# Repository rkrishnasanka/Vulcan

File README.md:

# Vulcan

This repository will hold all information regarding future microfluidic primitives. 
Please update the software and hardware readmes as well as the engineering addendum on completing a primitive.

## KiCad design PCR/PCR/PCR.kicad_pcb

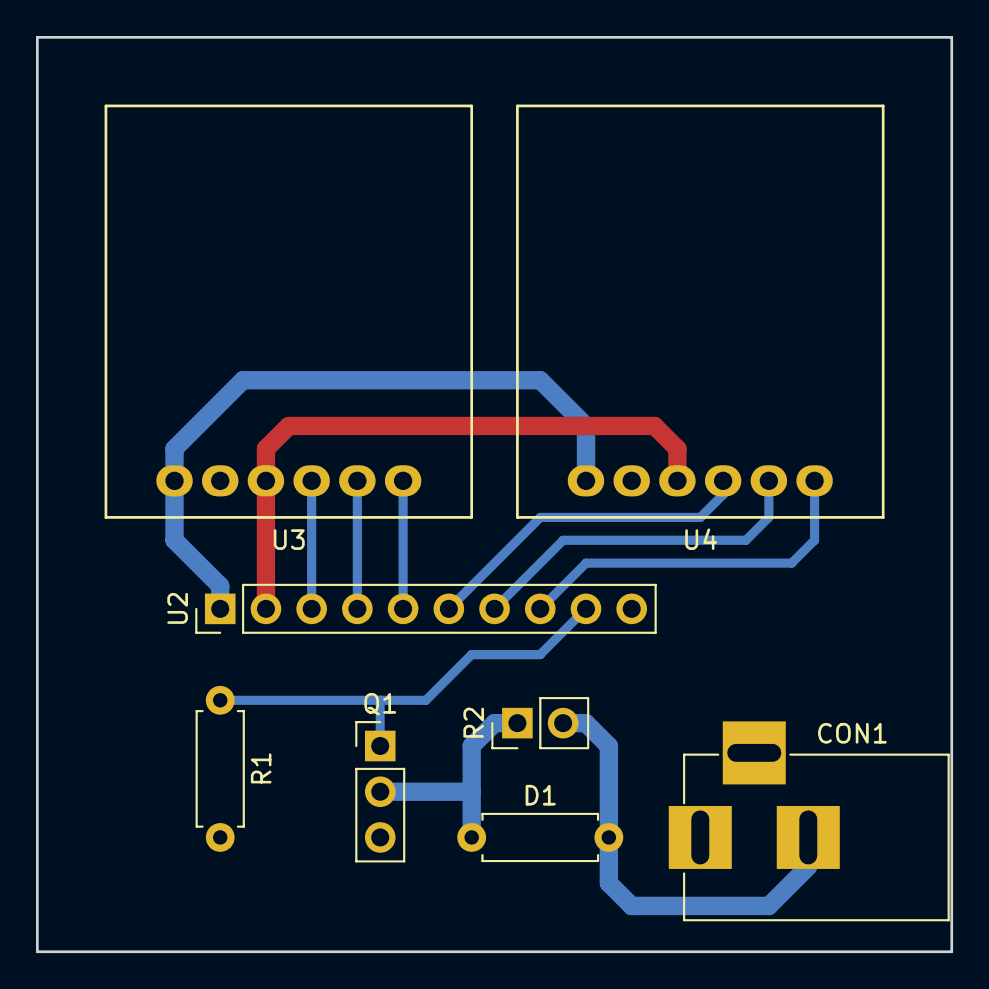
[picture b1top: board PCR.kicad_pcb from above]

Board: 2 copper layers, 50.8 x 50.8 mm, 8 parts (0 on the bottom side), 12 nets.

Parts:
CON1: BARREL_JACK
D1: D; R_Axial_DIN0207_L6.3mm_D2.5mm_P7.62mm_Horizontal
Q1: BUZ11; Pin_Header_Straight_1x03_Pitch2.54mm
R1: R; R_Axial_DIN0207_L6.3mm_D2.5mm_P7.62mm_Horizontal
R2: Nichrome Wire; Pin_Header_Straight_1x02_Pitch2.54mm
U2: Arduino; Arduino_Pin_Header_1x10
U3, U4: Amplifier; thermo_amp

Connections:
unnamed: CON1.1, Q1.3, R1.2, U2.16
unnamed: CON1.2, D1.2, R2.2
unnamed: D1.1, Q1.2, R2.1
unnamed: Q1.1, R1.1, U2.3
unnamed: U2.4, U4.6
unnamed: U2.5, U4.5
unnamed: U2.6, U4.4
unnamed: U2.10, U3.6
unnamed: U2.11, U3.5
unnamed: U2.12, U3.4
unnamed: U2.13, U3.1, U4.1
unnamed: U2.17, U3.3, U4.3

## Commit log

2016-11-13 Initial commit, pushing characterization stuff
2016-11-13 Added some text to the readme
2016-11-13 Created separate file for first deiliverables testing
2016-11-13 Updating readme, setting up git train stuff
2016-11-13 Testing out RGB values
2016-11-13 Issues with numpy array indexing
2016-11-15 Finished testing lul
2016-11-29 Updating the first deliverables code
2016-11-29 PCR beginning files in Arduino
2016-12-05 kicad
2017-01-10 Single Channel analysis
2017-01-10 Changing naming for clarity
2017-01-10 Changing naming for clarity [helloWorld/] -> [Characterization_Dev/]
2017-01-11 Created packages for format infrastructure
2017-01-17 Successfully characterizing y and x major videos, beginning to modularize and package functions
2017-01-17 Removing extraneous variables
2017-01-17 Organized computational functions into static utility class
2017-01-17 Integrated utility class function calls in programs
2017-01-25 Hello World with picam and microscope
2017-02-01 Fixed branch divergence, working on DE meeting / gather data for Ali
2017-02-02 Trying multiple techniques on video, no avail
2017-02-04 Messing around with new techniques, so close :')
2017-02-04 Drawing convex hulls, still seeing some disconnected regions, will need to look into combining close contours
2017-02-05 Got convex hulls to draw, no visible chages though.
2017-02-06 Multi thresholding and multi layer contour and convexHulls
2017-02-13 Testing configurations for multidroplet videos
2017-02-14 Significantly reduced multi counted droplets
2017-02-15 Readying the second deliverables tests
2017-02-27 State after DOug's Feb check-in, been neglecting to commit :/
2017-02-27 Refactoring for readability and comprehension
2017-02-27 Added counts between droplets (space between each) and counts during eclipses (how long a droplet takes to cross the zone)
2017-02-27 Adding a null video condition to default to connected camera (video0)
2017-02-28 Successful serial loopback test
2017-02-28 Successfully tested serial loop back with read / write loops
2017-02-28 Reformatted to use subprocess instead of os, which is its strict superset
2017-02-28 Appending to frame data to list
2017-03-02 Successful communication between laptop and raspberry pi (using UART)
2017-03-03 Tracking droplet size and speed characteristics
2017-03-03 Converted eclipse frames into droplet speed, added average # of droplets per second
2017-03-08 Output formatting :^)
2017-03-08 Removing .swp files..
2017-03-08 Added swp files to gitignore
2017-03-09 Sucessfully writing to csv and handling exceptions
2017-03-09 Working on the PI, verified serial I/O
2017-03-09 Modularizing the serial library for Vulcan / raspi
2017-03-09 Modularizing the line endings of serial output
2017-03-09 Unifying serial class into one KUMBAYA
2017-03-10 Adding fps stardardization, some clarity comments
2017-03-10 Fixed csv formatting and comments
2017-03-13 Applying signal handling to droplet detection
2017-03-15 Successful inter-process communication using python's subprocess and piping
2017-03-15 Got realtime stdout processing to work
2017-03-16 New PCB data
2017-03-17 Non-blocked readings and buffer/cache nullification
2017-03-17 Revised Schematic/PCB for PCR
2017-03-21 Got effective back and forth between Pi and manager
2017-03-28 Version 2 of the PCB
2017-04-17 Added video files to gitignore lol
2017-05-03 Pushing up some Pi stuff
2017-05-03 Culling videos
2017-05-18 Added docs
2017-05-18 Adding docs
2017-08-22 Renamed the PCB directory
